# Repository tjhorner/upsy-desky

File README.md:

# Upsy Desky 

This repository contains the source files for the Upsy Desky, a device which lets you connect your standing desk to any home automation system.

You can buy one on Tindie:

## Need Support?

If you need help with your Upsy Desky, please join the Upsy Desky [Discord server](https://discord.gg/ZHfXKQrSxF) where you can ask for help from the community and myself.

## Repository Structure

At the root of the repository you will find these directories:

- `pcb`: KiCad schematic and PCB design files (CC BY-NC-SA 4.0)
- `enclosure`: Fusion 360 design files and STLs for the enclosure (CC BY-NC-SA 4.0)
- `firmware`: ESPHome configuration files for the stock firmware (MIT)

With these you can make your own Upsy Desky from scratch, or you can make changes to the design and firmware to suit your needs. (If you do, I would love to see it!)

## What's new‽

This is the successor to the [WiFi Standing Desk Controller](https://github.com/tjhorner/wifi-desk-controller), packed with improvements and bug fixes — most notably:

- USB-C port for easy flashing (and because USB-C is cool 😎)
- Runtime firmware configuration -- no more manual flashing or compiling ESPHome to change stuff
- Improved enclosure design with a more snug fit and screw-mounted PCB, allowing for easier repairs and troubleshooting
- Replacing the D1 Mini with an ESP32-WROOM module, providing hardware UART for more reliable desk connection
- A catchier name, because "WiFi Standing Desk Controller" was a mouthful

This revision also fixes some annoying issues from the first version, such as the desk sometimes lowering on startup, or simply not powering at all without a hacky workaround.

## In a nutshell...

As with the original version of this product, it can connect your motorized standing desk to your home automation system. It can read your desk's current height, and set it as well. This lets you create automations that integrate with your desk, for example:

- If you're sitting for too long, raise desk to standing height
- When you leave home, raise desk to max height so the cat can't knock things over
- Have an infinite number of presets for everyone in your household
- Send desk height data to InfluxDB to analyze how often you're sitting vs. standing
- [Publish your desk's height on the internet](https://tjhorner.dev/sitting-or-standing/)

Or whatever else you'd like. The possibilities are endless! As long as the possibilities involve a standing desk.

## Compatibility

Any standing desk that uses RJ45 to connect to the keypad is likely compatible, but the control boxes listed [here](https://upsy-desky.tjhorner.dev/docs/reference/compatibility/) are verified to be compatible.

## Documentation

You can find everything you need in the [documentation](https://upsy-desky.tjhorner.dev/docs/getting-started/).

## Licenses

The ESPHome configs are licensed under MIT; everything else (enclosure and PCB design) are CC BY-NC-SA 4.0. The appropriate license files are available in the root of the repo.

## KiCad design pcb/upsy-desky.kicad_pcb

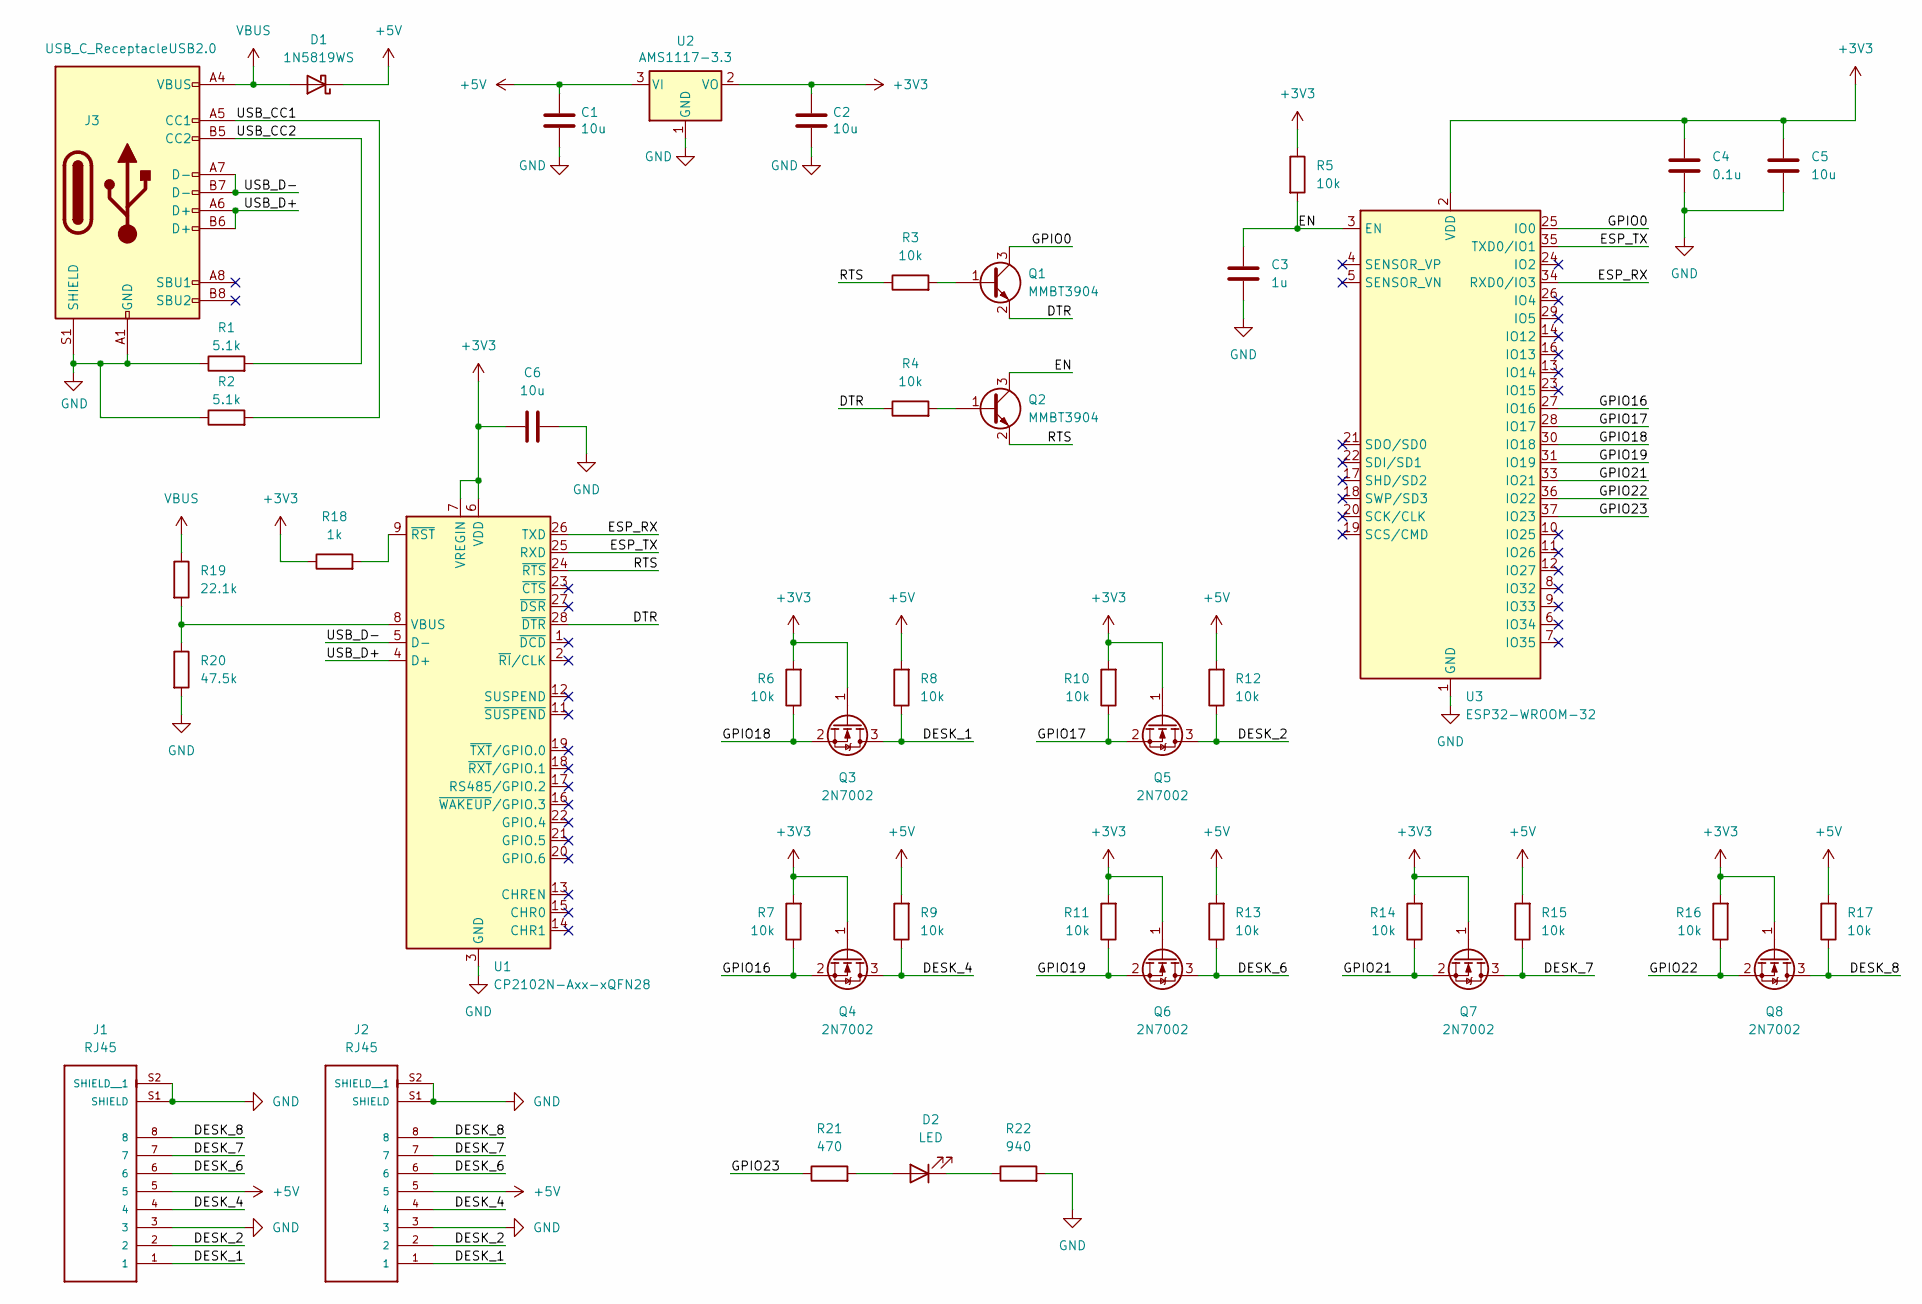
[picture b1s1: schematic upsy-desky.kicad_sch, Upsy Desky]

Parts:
C1, C2, C5, C6: 10u; C_0402_1005Metric; MPN GRM155R60J106ME05J; LCSC C15525
C3: 1u; C_0402_1005Metric; MPN 0402W105K100HI; LCSC C52923
C4: 0.1u; C_0402_1005Metric; MPN 0402B104K160HI; LCSC C1525
D1: 1N5819WS; D_SOD-323; MPN 1N5819WS; LCSC C191023
D2: LED; LED_0603_1608Metric; MPN LTST-C190KRKT; LCSC C2286
J1, J2: RJ45; ASSMANN_A-2004-2-4-LPS-N-R; PARTREV 00; LCSC C3000202
J3: USB_C_ReceptacleUSB2.0; USB_C_Receptacle_Palconn_UTC16-G; MPN TYPE-C-31-M-12; LCSC C165948
Q1, Q2: MMBT3904; SOT-23; MPN MMBT3904; LCSC C20526
Q3, Q4, Q5, Q6, Q7, Q8: 2N7002; SOT-23; MPN 2N7002; LCSC C8545
R1, R2: 5.1k; R_0402_1005Metric; MPN RC0402JR-075R1L; LCSC C25905
R3, R4, R5, R6, R7, R8, R9, R10, R11, R12, R13, R14, R15, R16, R17: 10k; R_0402_1005Metric; MPN RC0402JR-1310KL; LCSC C25744
R18: 1k; R_0402_1005Metric; MPN RC0402JR-131KL; LCSC C11702
R19: 22.1k; R_0402_1005Metric; MPN RC0402FR-1322K1L; LCSC C25768
R20: 47.5k; R_0402_1005Metric; MPN CR0402-FX-4752GLF; LCSC C25792
R21: 470; R_0402_1005Metric; MPN RC1005J471CS; LCSC C25117
R22: 940; R_0402_1005Metric; MPN RMCF0402FT953R; LCSC C11702
U1: CP2102N-Axx-xQFN28; QFN-28-1EP_5x5mm_P0.5mm_EP3.35x3.35mm; MPN CP2102N-Axx-xQFN28; LCSC C6568
U2: AMS1117-3.3; SOT-223-3_TabPin2; MPN AMS1117-3.3; LCSC C6186
U3: ESP32-WROOM-32; MPN ESP32-WROOM-32; LCSC C701341

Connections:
+3V3: C2.1, C4.1, C5.1, C6.1, Q3.1 (G), Q4.1 (G), Q5.1 (G), Q6.1 (G), Q7.1 (G), Q8.1 (G), R5.1, R6.2, R7.2, R10.2, R11.2, R14.2, R16.2, R18.1, U1.6 (VDD), U1.7 (VREGIN), U2.2 (VO), U3.2 (VDD)
+5V: C1.1, D1.1 (K), J1.5, J2.5, R8.2, R9.2, R12.2, R13.2, R15.2, R17.2, U2.3 (VI)
/DESK_1: J1.1, J2.1, Q3.3 (D), R8.1
/DESK_2: J1.2, J2.2, Q5.3 (D), R12.1
/DESK_4: J1.4, J2.4, Q4.3 (D), R9.1
/DESK_6: J1.6, J2.6, Q6.3 (D), R13.1
/DESK_7: J1.7, J2.7, Q7.3 (D), R15.1
/DESK_8: J1.8, J2.8, Q8.3 (D), R17.1
/DTR: Q1.2 (E), R4.1, U1.28 (~DTR)
/EN: C3.1, Q2.3 (C), R5.2, U3.3 (EN)
/ESP_RX: U1.26 (TXD), U3.34 (RXD0/IO3)
/ESP_TX: U1.25 (RXD), U3.35 (TXD0/IO1)
/GPIO0: Q1.3 (C), U3.25 (IO0)
/GPIO16: Q4.2 (S), R7.1, U3.27 (IO16)
/GPIO17: Q5.2 (S), R10.1, U3.28 (IO17)
/GPIO18: Q3.2 (S), R6.1, U3.30 (IO18)
/GPIO19: Q6.2 (S), R11.1, U3.31 (IO19)
/GPIO21: Q7.2 (S), R14.1, U3.33 (IO21)
/GPIO22: Q8.2 (S), R16.1, U3.36 (IO22)
/GPIO23: R21.1, U3.37 (IO23)
/RTS: Q2.2 (E), R3.1, U1.24 (~RTS)
/USB_CC1: J3.A5 (CC1), R2.2
/USB_CC2: J3.B5 (CC2), R1.2
/USB_D+: J3.A6 (D+), J3.B6 (D+), U1.4 (D+)
/USB_D-: J3.A7 (D-), J3.B7 (D-), U1.5 (D-)
GND: C1.2, C2.2, C3.2, C4.2, C5.2, C6.2, J1.3, J1.S1 (SHIELD), J1.S2 (SHIELD__1), J2.3, J2.S1 (SHIELD), J2.S2 (SHIELD__1), J3.A1 (GND), J3.A12 (GND), J3.B1 (GND), J3.B12 (GND), J3.S1 (SHIELD), R1.1, R2.1, R20.2, R22.2, U1.3 (GND), U1.29 (GND), U2.1 (GND), U3.1 (GND), U3.15 (GND), U3.38 (GND), U3.39 (GND)
unnamed: D2.1 (K), R22.1
unnamed: D2.2 (A), R21.2
unnamed: Q1.1 (B), R3.2
unnamed: Q2.1 (B), R4.2
unnamed: R18.2, U1.9 (~RST)
unnamed: R19.2, R20.1, U1.8 (VBUS)
VBUS: D1.2 (A), J3.A4 (VBUS), J3.A9 (VBUS), J3.B4 (VBUS), J3.B9 (VBUS), R19.1

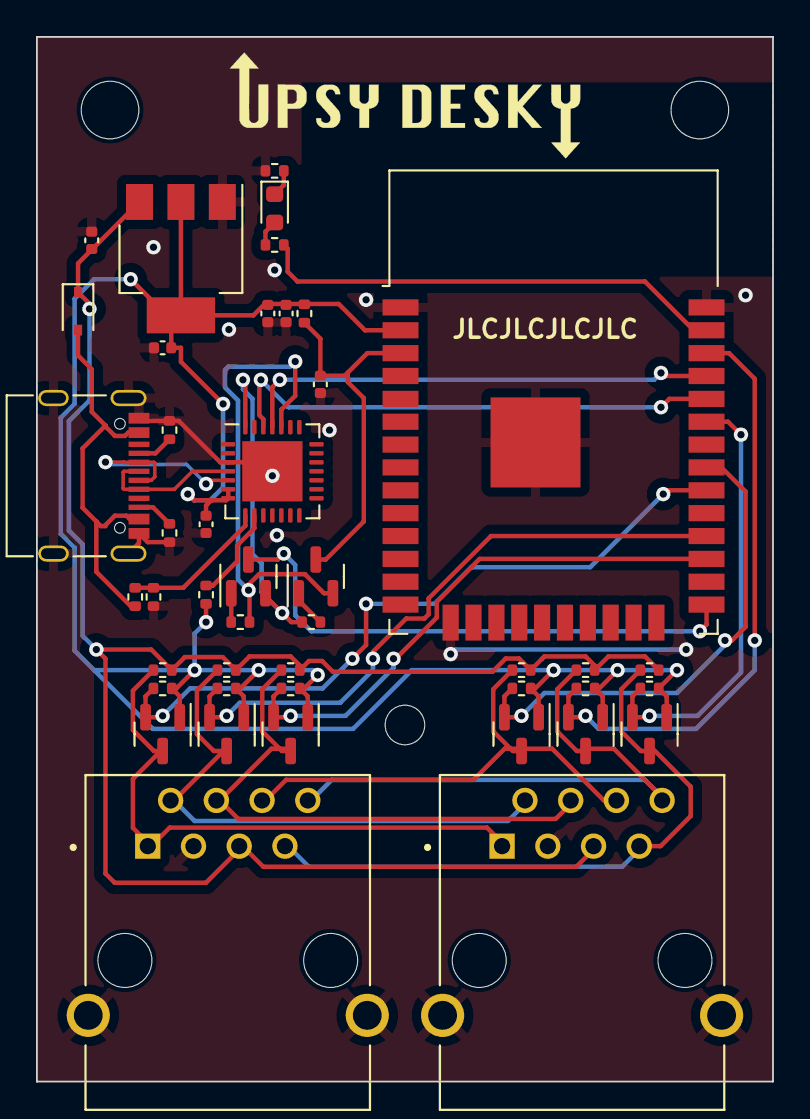
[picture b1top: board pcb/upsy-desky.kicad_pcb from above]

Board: 2 copper layers, 40.9 x 58.0 mm, 45 parts (0 on the bottom side), 33 nets.

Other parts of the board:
Ref**: Val**; dark_logotype_horizontal

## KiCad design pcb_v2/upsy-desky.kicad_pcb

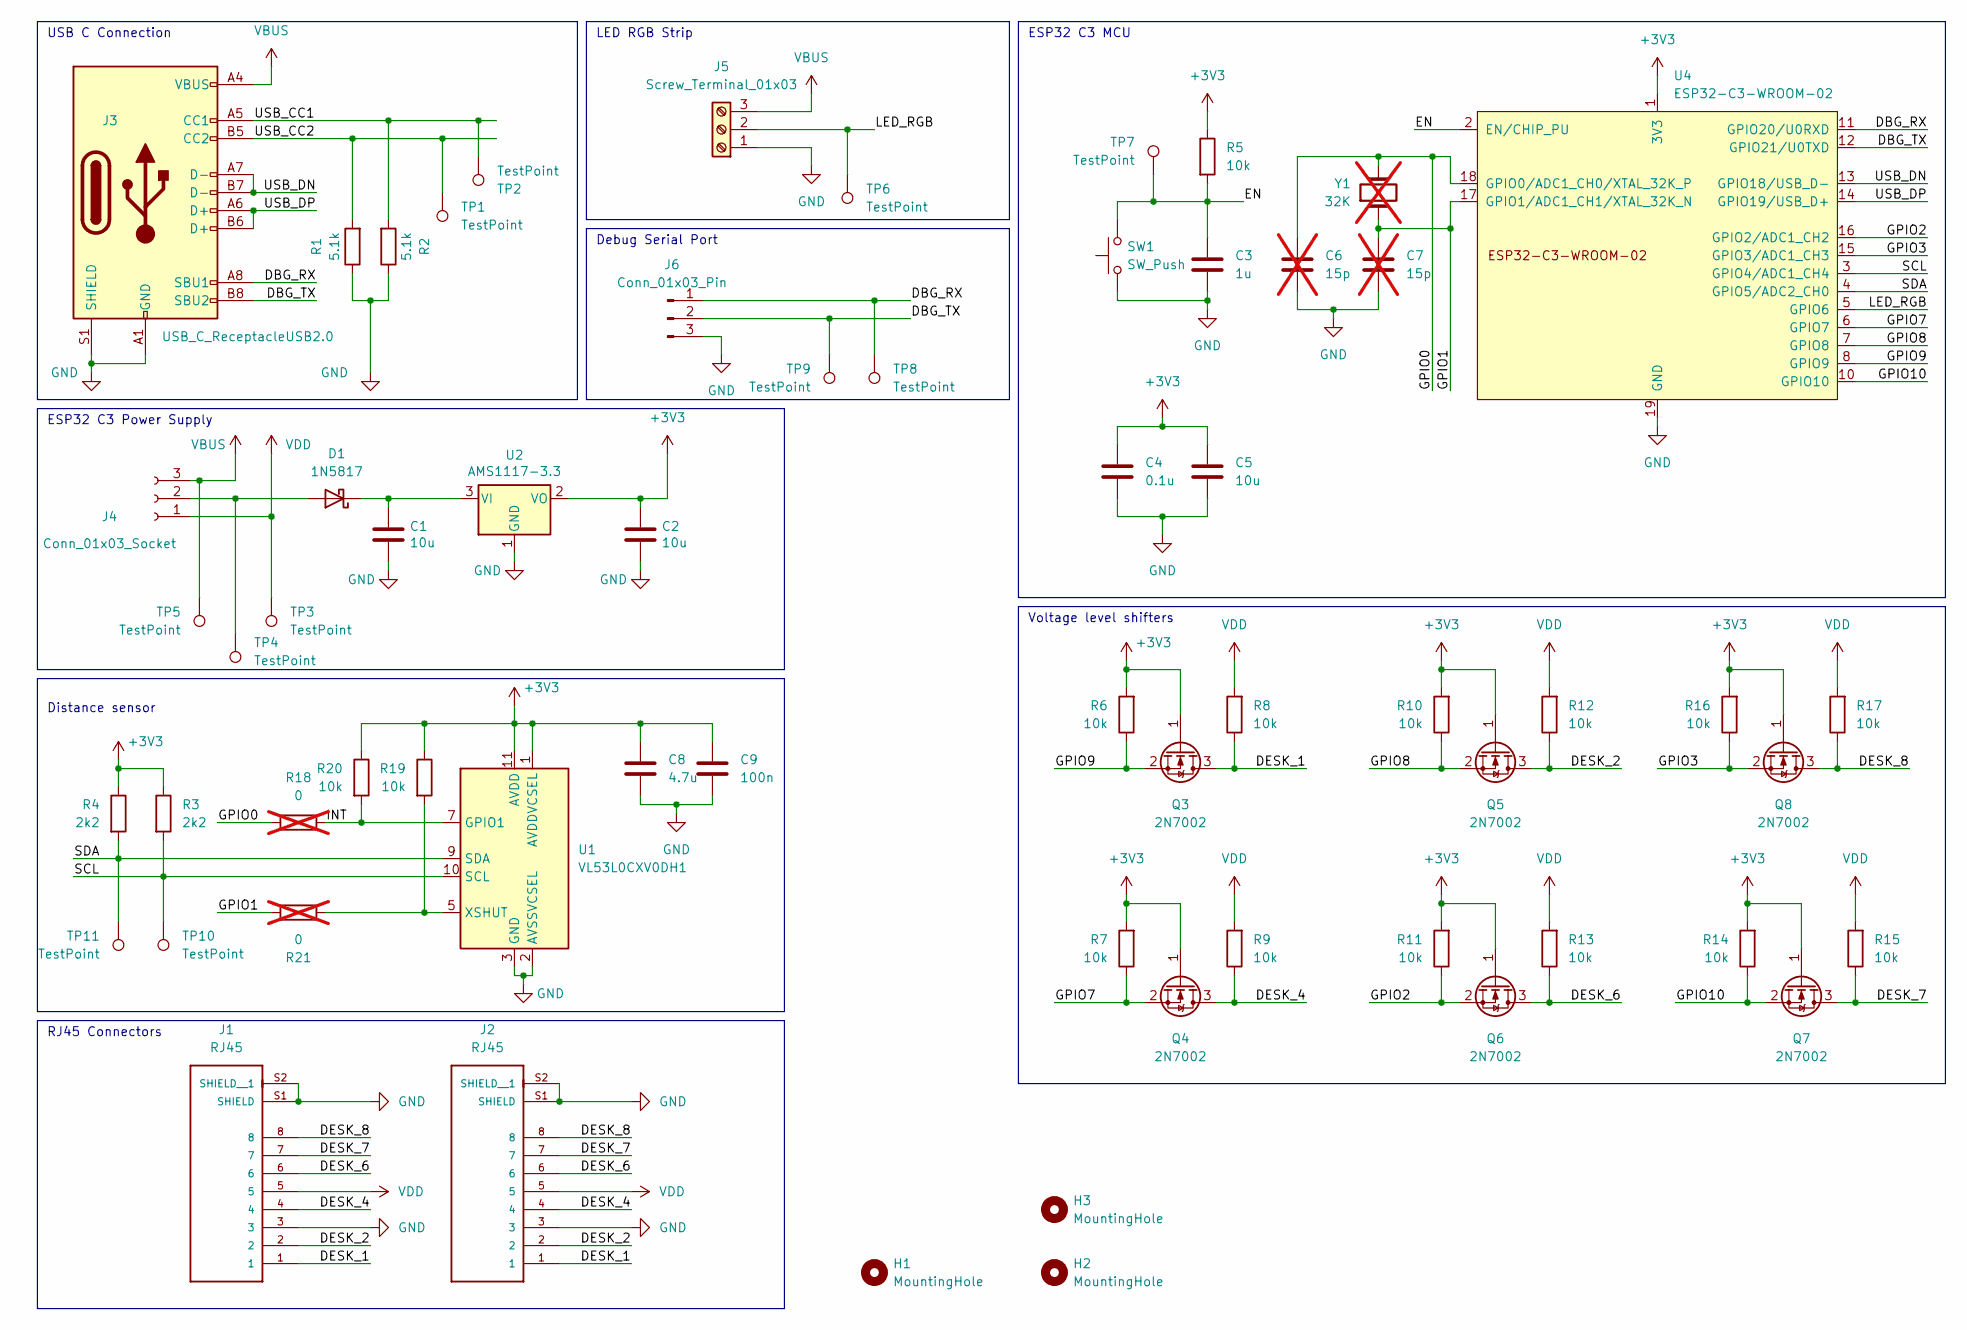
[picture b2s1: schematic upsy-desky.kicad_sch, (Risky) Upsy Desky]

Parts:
C1, C2, C5: 10u; C_0402_1005Metric; MPN GRM155R60J106ME05J; LCSC C15525
C3: 1u; C_0402_1005Metric; MPN 0402W105K100HI; LCSC C52923
C4: 0.1u; C_0402_1005Metric; MPN 0402B104K160HI; LCSC C1525
C6, C7: 15p; C_0402_1005Metric; not fitted
C8: 4.7u; C_0402_1005Metric
C9: 100n; C_0402_1005Metric
D1: 1N5817; D_SOD-323; MPN 1N5817; LCSC C191023
H1, H2, H3: MountingHole; MountingHole_2.2mm_M2_Pad
J1, J2: RJ45; RJ45_Amphenol_54602-x08_Horizontal; PARTREV 00; LCSC C708595
J3: USB_C_ReceptacleUSB2.0; USB_C_Receptacle_Palconn_UTC16-G; MPN TYPE-C-31-M-12; LCSC C165948
J4: Conn_01x03_Socket; FanPinHeader_1x03_P2.54mm_Vertical
J5: Screw_Terminal_01x03; TerminalBlock_Altech_AK300-3_P5.00mm
J6: Conn_01x03_Pin; JST_EH_B3B-EH-A_1x03_P2.50mm_Vertical
Q3, Q4, Q5, Q6, Q7, Q8: 2N7002; SOT-23; MPN 2N7002; LCSC C8545
R1, R2: 5.1k; R_0402_1005Metric; MPN RC0402JR-075R1L; LCSC C25905
R3, R4: 2k2; R_0402_1005Metric
R5, R6, R7, R8, R9, R10, R11, R12, R13, R14, R15, R16, R17: 10k; R_0402_1005Metric; MPN RC0402JR-1310KL; LCSC C25744
R18, R21: 0; R_0402_1005Metric; not fitted
R19, R20: 10k; R_0402_1005Metric
SW1: SW_Push; SW_Push_1P1T_NO_CK_KMR2
TP1, TP2, TP3, TP4, TP5, TP6, TP7, TP8, TP9, TP10, TP11: TestPoint; TestPoint_Pad_D1.0mm
U1: VL53L0CXV0DH1; ST_VL53L1x
U2: AMS1117-3.3; SOT-223-3_TabPin2; MPN AMS1117-3.3; LCSC C6186
U4: ESP32-C3-WROOM-02
Y1: 32K; Crystal_SMD_2012-2Pin_2.0x1.2mm; not fitted

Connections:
+3V3: C2.1, C4.1, C5.1, C8.1, C9.1, Q3.1 (G), Q4.1 (G), Q5.1 (G), Q6.1 (G), Q7.1 (G), Q8.1 (G), R3.1, R4.1, R5.1, R6.2, R7.2, R10.2, R11.2, R14.2, R16.2, R19.1, R20.1, U1.1 (AVDDVCSEL), U1.11 (AVDD), U2.2 (VO), U4.1 (3V3)
/DBG_RX: J3.A8 (SBU1), J6.1, TP8.1, U4.11 (GPIO20/U0RXD)
/DBG_TX: J3.B8 (SBU2), J6.2, TP9.1, U4.12 (GPIO21/U0TXD)
/DESK_1: J1.1, J2.1, Q3.3 (D), R8.1
/DESK_2: J1.2, J2.2, Q5.3 (D), R12.1
/DESK_4: J1.4, J2.4, Q4.3 (D), R9.1
/DESK_6: J1.6, J2.6, Q6.3 (D), R13.1
/DESK_7: J1.7, J2.7, Q7.3 (D), R15.1
/DESK_8: J1.8, J2.8, Q8.3 (D), R17.1
/EN: C3.1, R5.2, SW1.2, TP7.1, U4.2 (EN/CHIP_PU)
/GPIO0: C6.1, R18.2, U4.18 (GPIO0/ADC1_CH0/XTAL_32K_P), Y1.2
/GPIO1: C7.1, R21.2, U4.17 (GPIO1/ADC1_CH1/XTAL_32K_N), Y1.1
/GPIO2: Q6.2 (S), R11.1, U4.16 (GPIO2/ADC1_CH2)
/GPIO3: Q8.2 (S), R16.1, U4.15 (GPIO3/ADC1_CH3)
/GPIO7: Q4.2 (S), R7.1, U4.6 (GPIO7)
/GPIO8: Q5.2 (S), R10.1, U4.7 (GPIO8)
/GPIO9: Q3.2 (S), R6.1, U4.8 (GPIO9)
/GPIO10: Q7.2 (S), R14.1, U4.10 (GPIO10)
/INT: R18.1, R20.2, U1.7 (GPIO1)
/LED_RGB: J5.2, TP6.1, U4.5 (GPIO6)
/SCL: R3.2, TP10.1, U1.10 (SCL), U4.3 (GPIO4/ADC1_CH4)
/SDA: R4.2, TP11.1, U1.9 (SDA), U4.4 (GPIO5/ADC2_CH0)
/USB_CC1: J3.A5 (CC1), R2.2, TP2.1
/USB_CC2: J3.B5 (CC2), R1.2, TP1.1
/USB_DN: J3.A7 (D-), J3.B7 (D-), U4.13 (GPIO18/USB_D-)
/USB_DP: J3.A6 (D+), J3.B6 (D+), U4.14 (GPIO19/USB_D+)
GND: C1.2, C2.2, C3.2, C4.2, C5.2, C6.2, C7.2, C8.2, C9.2, J1.3, J1.S1 (SHIELD), J1.S2 (SHIELD__1), J2.3, J2.S1 (SHIELD), J2.S2 (SHIELD__1), J3.A1 (GND), J3.A12 (GND), J3.B1 (GND), J3.B12 (GND), J3.S1 (SHIELD), J5.1, J6.3, R1.1, R2.1, SW1.1, U1.2 (AVSSVCSEL), U1.3 (GND), U1.4 (GND), U1.6 (GND), U1.12 (GND), U2.1 (GND), U4.9 (GND), U4.19 (GND)
unnamed: D1.2 (A), J4.2, TP4.1
unnamed: C1.1, D1.1 (K), U2.3 (VI)
unnamed: R19.2, R21.1, U1.5 (XSHUT)
VBUS: J3.A4 (VBUS), J3.A9 (VBUS), J3.B4 (VBUS), J3.B9 (VBUS), J4.3, J5.3, TP5.1
VDD: J1.5, J2.5, J4.1, R8.2, R9.2, R12.2, R13.2, R15.2, R17.2, TP3.1

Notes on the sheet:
ESP32 C3 MCU
Debug Serial Port
RJ45 Connectors
USB C Connection
LED RGB Strip
Distance sensor
Voltage level shifters
ESP32 C3 Power Supply

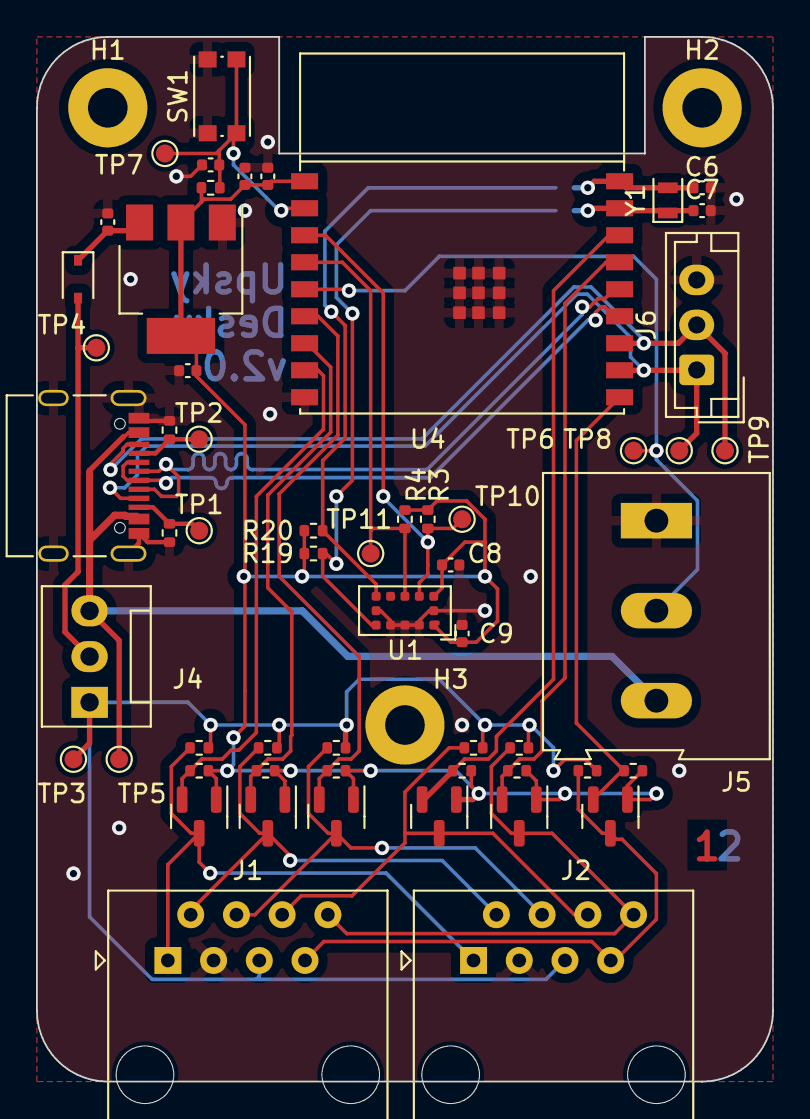
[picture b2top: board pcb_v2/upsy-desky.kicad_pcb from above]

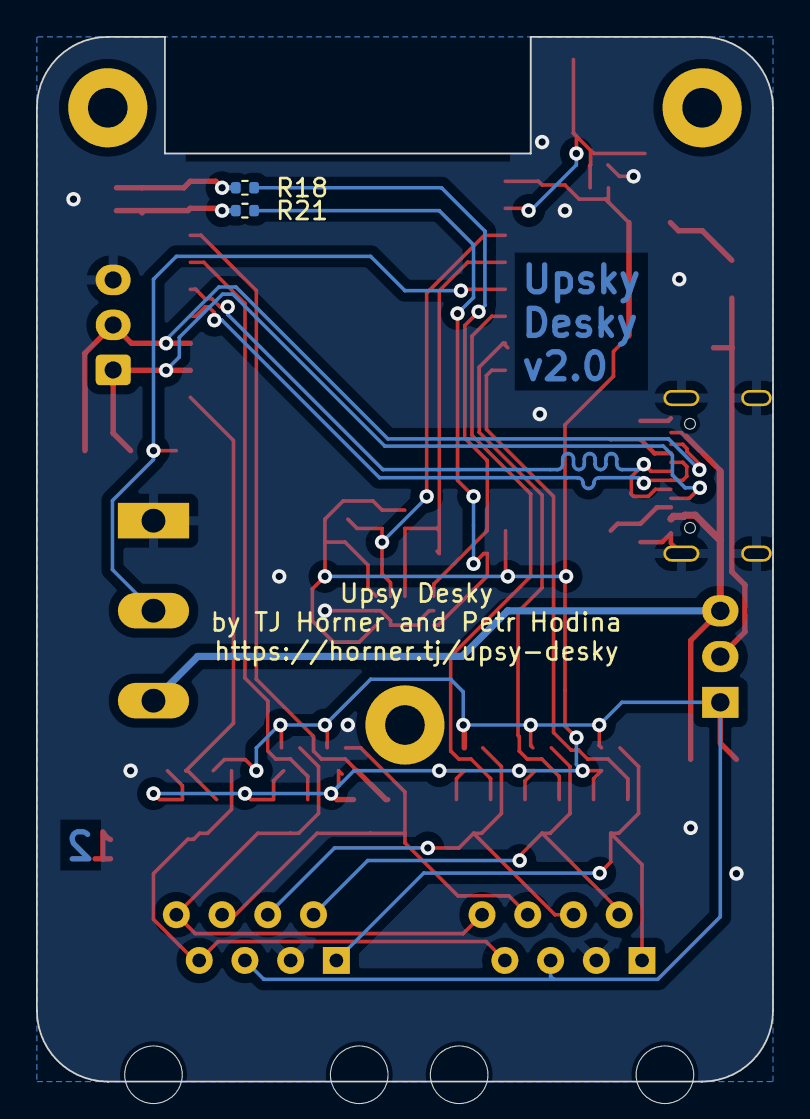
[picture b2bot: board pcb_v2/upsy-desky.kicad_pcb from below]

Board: 2 copper layers, 40.9 x 58.0 mm, 62 parts (2 on the bottom side), 32 nets.

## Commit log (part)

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2022-08-23 Initial firmware stuff
2022-08-23 Use firmware-factory
2022-08-26 pcb, enclosure files
2022-08-26 license
2022-08-26 update enclosure to not model screw holes
2022-08-26 update fusion source
2022-08-26 readme good
2022-08-26 does that look good on github
2022-08-26 lil bit wider
2022-08-27 Update readme to clarify
2022-08-28 Update stock firmware to use substitutions for name
2022-08-28 Bump firmware to 0.0.3
2022-08-28 Copypasta error
2022-08-29 Runtime configuration variables for firmware
2022-08-30 readme update
2022-09-19 Fix #10
2022-10-01 Debug firmware
2022-10-01 add support email to readme
2022-10-01 Add test firmware and pcb changes
2022-10-11 Update firmware with new timeout
2022-10-28 Firmware 0.2.0
2023-02-01 misc PCB updates
2023-02-01 fulfillment docs
2023-02-01 RE firmware
2023-02-01 Update doc links
2023-02-01 Update enclosure STLs
2023-02-01 Add omnidesk decoder option
2023-02-16 Firmware 0.3.0
2023-02-25 0.3.1 RC
2023-02-25 Move dashboard_import to stock config
2023-02-25 Rename the IDs for desk presets
2023-02-25 Don't import full config on dashboard import
2023-02-26 0.4.0
2023-02-26 Add flashing script
2023-03-01 More tools docs
2023-03-12 Add Bluetooth Proxy support to stock firmware
2023-03-12 Auto detection beta
2023-03-12 Add runtime config button to re-detect decoder
2023-03-12 Firmware 1.0.0
2023-03-12 Update package_import_url
2023-05-18 Fix runtime config addon for ESPHome 2023.5
2023-05-18 Version 1.0.1
2023-05-18 Enforce min ESPHome version 2023.5.1
2023-05-21 Remove "Height Units" from runtime config temporarily
2023-05-21 Re-add height units config with new method
2023-05-21 Add height units config back with fixes
2023-05-21 Various PCB and tools changes, unrelated to firmware
2023-05-21 Version 1.0.3
2023-05-22 Firmware and readme changes
2023-05-22 Version 1.0.4
2023-05-22 Project version component test
2023-05-23 tindie tools update
2023-05-23 Version 1.1.0
2023-05-23 Version 1.1.1
2023-05-23 Obtain custom component from GitHub instead of relative path
2023-05-23 Switch to using second repository for project_version component
2023-05-27 Add bug report issue template
2023-05-27 Rearrange bug report template
2023-05-27 I hope the template supports markdown in the description
2023-05-27 Change issue template description
2023-05-27 Add nightly build to ensure it always works with latest ESPHome
2023-10-31 Firmware 1.1.2
2023-11-01 Disable bluetooth proxy active connections by default in stock firmware
2023-11-09 Add GH Sponsors
2023-12-17 Add ESPHome 2023.12 compatibility
2023-12-21 Version 2.0.0
2023-12-21 Version for users on ESPHome <2023.12
2023-12-25 Add copy of the PCB for version 2
2023-12-26 Modify the schematics
2023-12-26 Modify the layout
2023-12-29 Several improvements:
    - Improved GND connection to the ESP32 module.
    - Connected the UART signals to SBU pins.
    - Rounded corners
2024-01-06 Minor fixes to edge cut layer
2024-01-06 Add lock files to gitignore
2024-01-06 Remove lockfiles
2024-01-23 Update tindie csv tool for new shipping options
2024-04-01 Fix error in BOM - closes #45
2024-06-06 make test firmware quicker
2024-06-06 switch to esp-idf; remove Bluetooth Proxy by default
2024-06-20 Fixed ESPHome 2024.6.0 breaking change where OTA requires platform
    The ESPHome OTA component has a breaking change in 2024.6.0 where the platform needs to be defined
    https://esphome.io/changelog/2024.6.0.html#ota-platforms
2024-06-20 v4.0.0
2024-06-20 fix release workflow
2024-07-01 ci: fix nightly builds
2024-07-06 Switch to heirarchical layout - add usb, controller and connectors sheets.
2024-07-06 Replace schematic RJ45 with symbol from the library
2024-07-22 Connect pin sheets. Add protection on USB. Use SolderJumpers.
2024-11-25 chore: bump version to 4.0.1
2024-12-01 pcb: Update RJ45 part number
2024-12-01 pcb: slight revision with logo on silkscreen
2024-12-15 fix: update for breaking change in 2024.12.0b1
2025-05-11 remove boot wakeup message for testing
2026-03-19 Remove offending section
2026-03-19 fix: update runtime-config for ESPHome 2026.3.0 breaking changes
    - Replace deprecated Select::state with current_option()
    - Remove set_unit_of_measurement() calls (immutable after init in 2026.3)
    - Remove traits.set_min_value/set_max_value() calls (immutable in 2026.3)
    - Add component IDs to min/max height number templates
2026-03-19 update actions/upload-artifact action
2026-03-19 fix: remove dynamic units of measurement
2026-03-19 bump python version in CI
2026-03-20 automatically substitute version number in CD pipeline
